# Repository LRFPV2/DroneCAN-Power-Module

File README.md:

# XRC Technologies DroneCAN Power Module

INSTRUCTIONS FOR USE: 
Checkout code and submodules. If sub-modules are not checked out, code will not compile properly due to broken dependencies.
```
git clone --recurse-submodules https://github.com/LRFPV2/DroneCAN-Power-Module.git
```
To flash to device, open project in PlatformIO and build "Micro-Node-No-Bootloader"

Go into STM32CubeIDE and open the file "firmware.bin" from folder .pio

Select "Download" to program to STM32 after connecting.

Version 2.0 to be released soon at https://xrctechnologies.com/

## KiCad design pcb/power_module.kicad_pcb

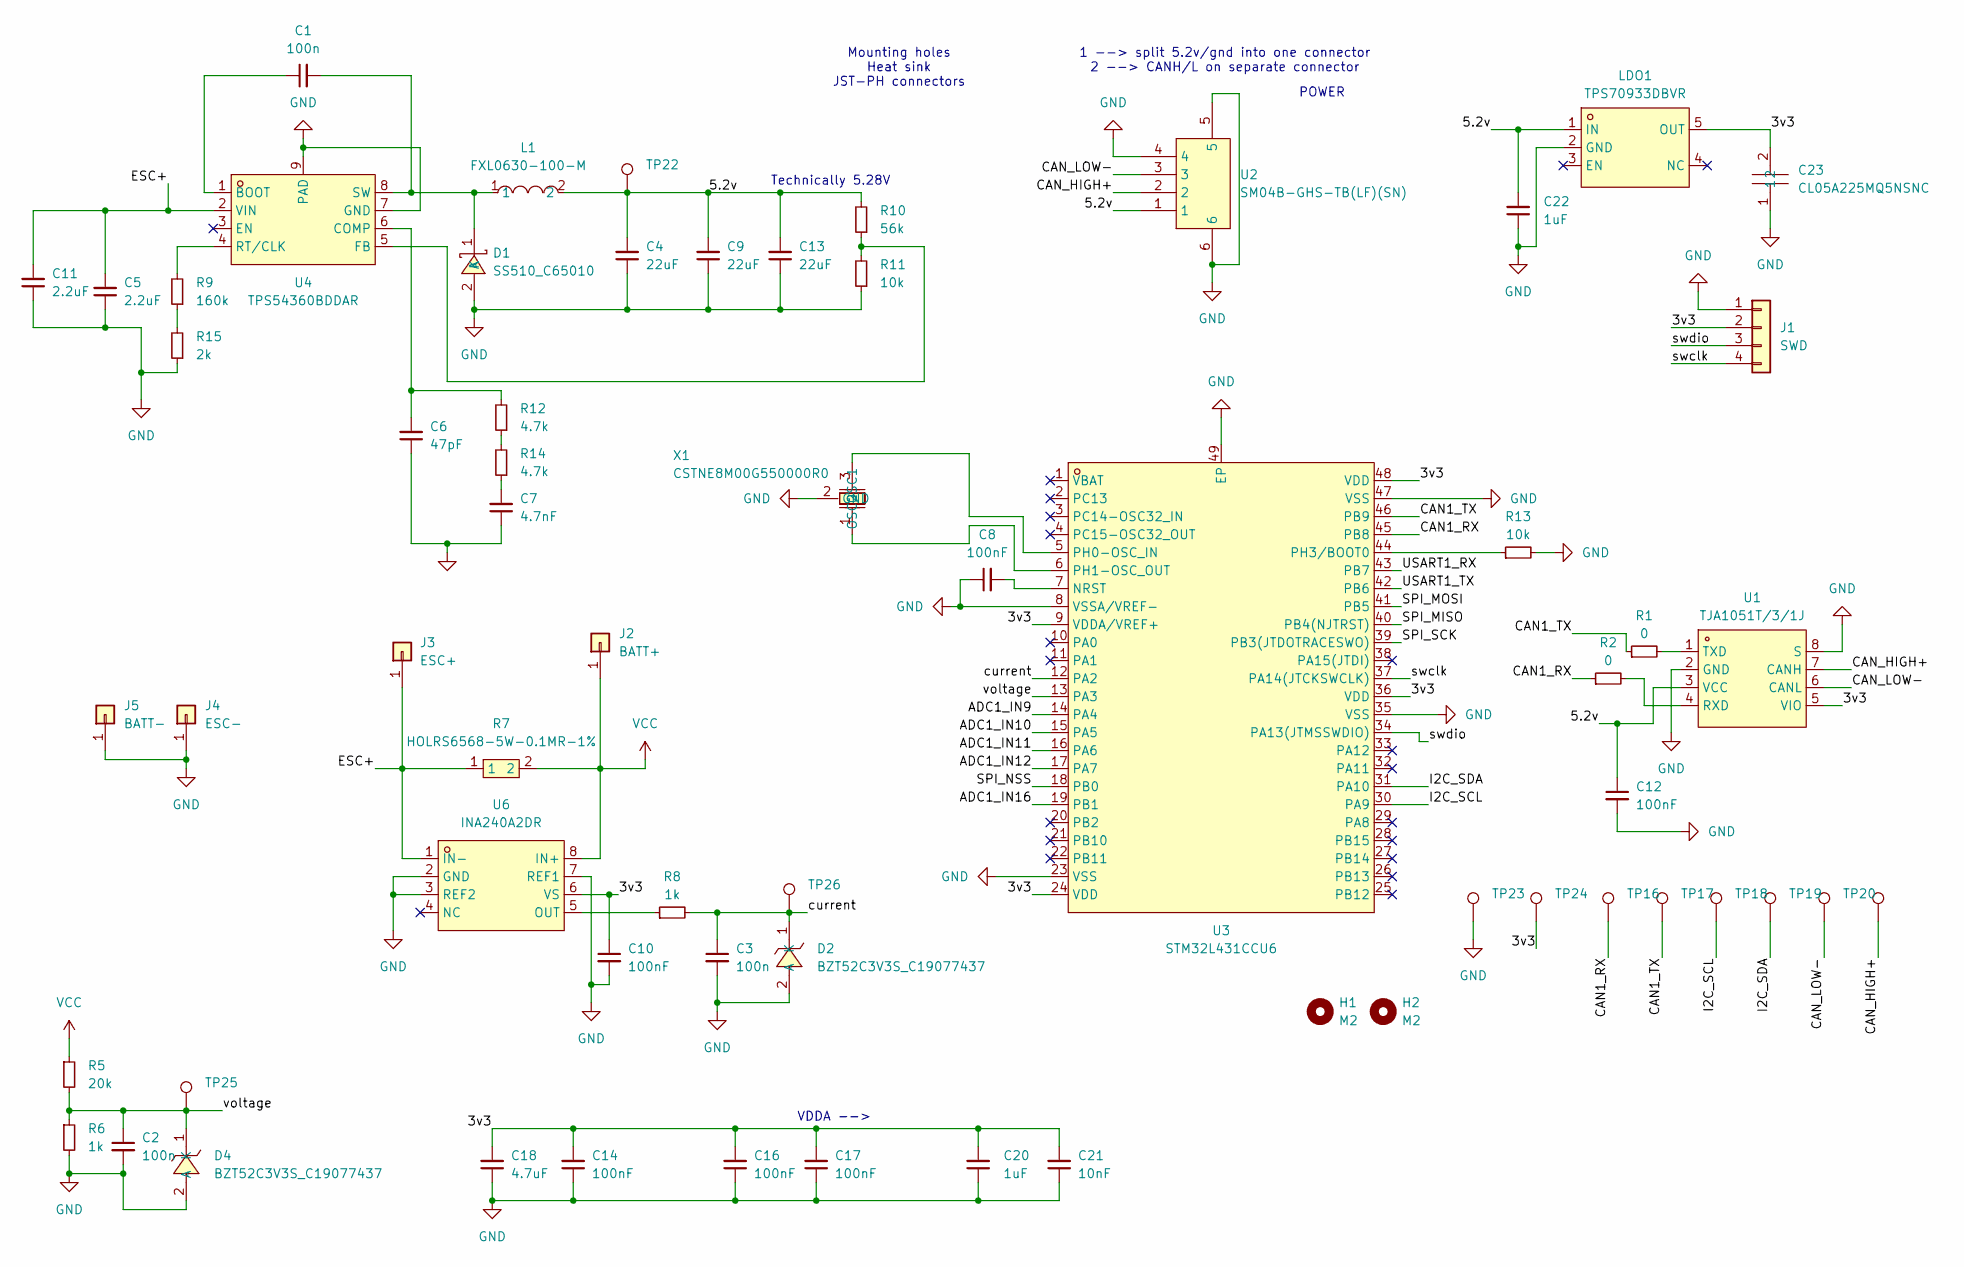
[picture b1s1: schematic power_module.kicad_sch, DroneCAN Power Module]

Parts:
C1, C2, C3: 100n; C_0402_1005Metric
C4, C9, C13: 22uF; C_0805_2012Metric
C5, C11: 2.2uF; C_1210_3225Metric
C6: 47pF; C_0402_1005Metric
C7: 4.7nF; C_0402_1005Metric
C8, C10, C12, C14, C16, C17: 100nF; C_0402_1005Metric
C18: 4.7uF; C_0402_1005Metric
C20, C22: 1uF; C_0402_1005Metric
C21: 10nF; C_0402_1005Metric
C23: CL05A225MQ5NSNC; C0402; LCSC Part C12530
D1: SS510_C65010; SMA_L4.3-W2.6-LS5.2-RD; LCSC Part C65010
D2, D4: BZT52C3V3S_C19077437; SOD-323_L1.7-W1.3-LS2.6-RD; LCSC Part C19077437
H1, H2: M2; MountingHole_2.2mm_M2
J1: SWD; PinHeader_1x04_P1.00mm_Vertical
J2: BATT+; Big-pad-0
J3: ESC+; Big-pad-0
J4: ESC-; Big-pad-0
J5: BATT-; Big-pad-0
L1: FXL0630-100-M; IND-SMD_L7.3-W6.8; LCSC Part C167223
LDO1: TPS70933DBVR; SOT-23-5_L3.0-W1.7-P0.95-LS2.8-BR; LCSC Part C89347
R1, R2: 0; R_0402_1005Metric
R5: 20k; R_0603_1608Metric
R6, R8: 1k; R_0402_1005Metric
R7: HOLRS6568-5W-0.1MR-1%; RES-SMD_L6.9-W6.6-A; LCSC Part C2927618
R9: 160k; R_0603_1608Metric
R10: 56k; R_0805_2012Metric
R11, R13: 10k; R_0402_1005Metric
R12, R14: 4.7k; R_0603_1608Metric
R15: 2k; R_0603_1608Metric
TP16, TP17, TP18, TP19, TP20, TP21, TP22, TP23, TP24, TP25, TP26: TestPoint_Pad_D1.0mm
U1: TJA1051T/3/1J; SOIC-8_L4.9-W3.9-P1.27-LS6.0-BL; LCSC Part C38695
U2: SM04B-GHS-TB(LF)(SN); CONN-SMD_4P-P1.25_SM04B-GHS-TB-LF-SN; LCSC Part C189895
U3: STM32L431CCU6; VQFN-48_L7.0-W7.0-P0.50-BL-EP5.5; LCSC Part C1337258
U4: TPS54360BDDAR; SOIC-8_L5.0-W4.0-P1.27-LS6.0-BL-EP2.0; LCSC Part C524806
U6: INA240A2DR; SOIC-8_L4.9-W3.9-P1.27-LS6.0-BL; LCSC Part C2060768
X1: CSTNE8M00G550000R0; OSC-SMD_3P-L3.2-W1.3-P1.20-L; LCSC Part C341522

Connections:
/3v3: C10.1, C14.2, C16.2, C17.2, C18.2, C20.2, C21.2, C23.2, J1.2, LDO1.5 (OUT), TP24.1, U1.5 (VIO), U3.9 (VDDA/VREF+), U3.24 (VDD), U3.36 (VDD), U3.48 (VDD), U6.6 (VS)
/5.2v: C4.2, C9.2, C12.1, C13.2, C22.2, L1.2, LDO1.1 (IN), R10.2, TP22.1, U1.3 (VCC), U2.1
/ADC1_IN9: U3.14 (PA4)
/ADC1_IN10: U3.15 (PA5)
/ADC1_IN11: U3.16 (PA6)
/ADC1_IN12: U3.17 (PA7)
/ADC1_IN16: U3.19 (PB1)
/CAN1_RX: R2.1, TP16.1, U3.45 (PB8)
/CAN1_TX: R1.1, TP17.1, U3.46 (PB9)
/CAN_HIGH+: TP21.1, U1.7 (CANH), U2.2
/CAN_LOW-: TP20.1, U1.6 (CANL), U2.3
/ESC+: C5.2, C11.2, J3.1, R7.1, U4.2 (VIN), U6.1 (IN-)
/I2C_SCL: TP18.1, U3.30 (PA9)
/I2C_SDA: TP19.1, U3.31 (PA10)
/SPI_MISO: U3.40 (PB4(NJTRST))
/SPI_MOSI: U3.41 (PB5)
/SPI_NSS: U3.18 (PB0)
/SPI_SCK: U3.39 (PB3(JTDOTRACESWO))
/USART1_RX: U3.43 (PB7)
/USART1_TX: U3.42 (PB6)
/current: C3.1, D2.1 (K), R8.2, TP26.1, U3.12 (PA2)
/swclk: J1.4, U3.37 (PA14(JTCKSWCLK))
/swdio: J1.3, U3.34 (PA13(JTMSSWDIO))
/voltage: C2.1, D4.1 (K), R5.2, R6.1, TP25.1, U3.13 (PA3)
GND: C2.2, C3.2, C4.1, C5.1, C6.1, C7.1, C8.1, C9.1, C10.2, C11.1, C12.2, C13.1, C14.1, C16.1, C17.1, C18.1, C20.1, C21.1, C22.1, C23.1, D1.2 (A), D2.2 (A), D4.2 (A), J1.1, J4.1, J5.1, LDO1.2 (GND), R6.2, R11.1, R13.2, R15.1, TP23.1, U1.2 (GND), U1.8 (S), U2.4, U2.5, U2.6, U3.8 (VSSA/VREF-), U3.23 (VSS), U3.35 (VSS), U3.47 (VSS), U3.49 (EP), U4.7 (GND), U4.9 (PAD), U6.2 (GND), U6.3 (REF2), U6.7 (REF1), X1.2 (GND)
unnamed: C7.2, R14.1
unnamed: C1.2, D1.1 (K), L1.1, U4.8 (SW)
unnamed: R12.1, R14.2
unnamed: R9.1, R15.2
unnamed: R2.2, U1.4 (RXD)
unnamed: R1.2, U1.1 (TXD)
unnamed: C8.2, U3.7 (NRST)
unnamed: U3.5 (PH0-OSC_IN), X1.3 (OSC2)
unnamed: U3.6 (PH1-OSC_OUT), X1.1 (OSC1)
unnamed: R13.1, U3.44 (PH3/BOOT0)
unnamed: C1.1, U4.1 (BOOT)
unnamed: C6.2, R12.2, U4.6 (COMP)
unnamed: R10.1, R11.2, U4.5 (FB)
unnamed: R9.2, U4.4 (RT/CLK)
unnamed: R8.1, U6.5 (OUT)
VCC: J2.1, R5.1, R7.2, U6.8 (IN+)

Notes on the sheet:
Mounting holes Heat sink JST-PH connectors
Technically 5.28V
POWER
VDDA -->
1 --> split 5.2v/gnd into one connector 2 --> CANH/L on separate connector

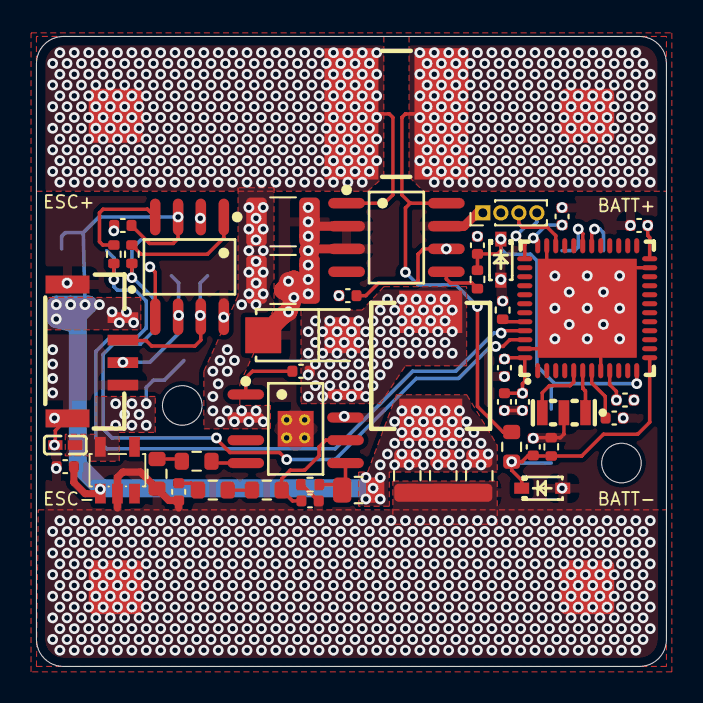
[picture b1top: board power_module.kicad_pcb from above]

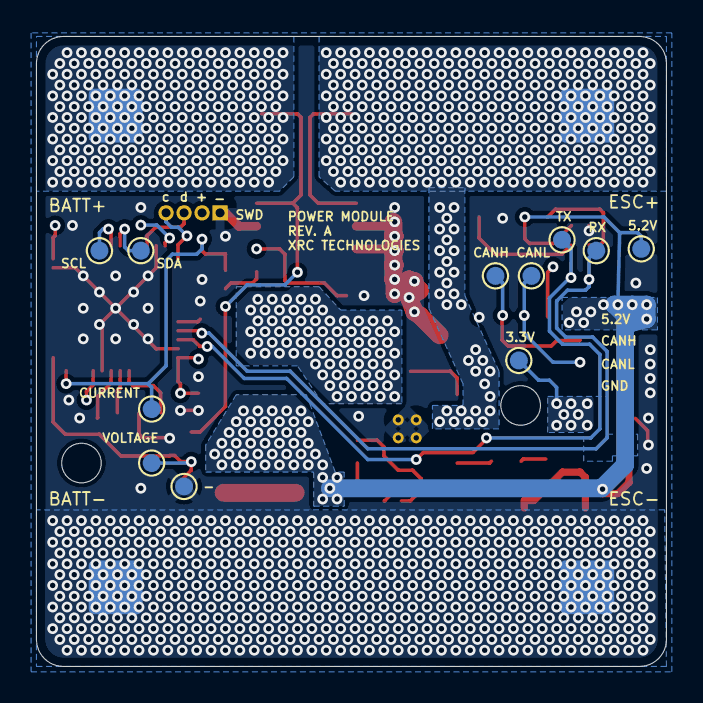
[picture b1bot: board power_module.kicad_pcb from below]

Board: 6 copper layers, 35.0 x 35.0 mm, 63 parts (11 on the bottom side), 30 nets.

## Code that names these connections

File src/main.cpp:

// XRC Technologies DroneCAN Power Module

#include <Arduino.h>
#include <dronecan.h>
#include <IWatchdog.h>
#include <app.h>
#include <vector>
#include <simple_dronecanmessages.h>

// Calculations:
// 0.1mOhm resistor
// 20k-1k voltage divider
// Vout = Vbatt / 21
// 12-bit ADC (4096 bit resolution)
// INA240A2 --> 50V/V Gain
// Voltage (ADC)= I * 0.0001 * 50 = 3.3/4096
// Voltage (ADC) = 3.3/4096 = V_batt / 21
// Target current: 200A
// These are good starting numbers but actual numbers may vary
// I_batt = 0.0064453125 * V_adc
// V_batt = 0.0169189453125 * V_adc
// 1 / I_batt constant = 155.151515
// 1 / V_batt constant = 59.1053391

#define SHUNT_RESISTANCE 0.0025
#define CURRENT_SCALE_FACTOR 1.623
#define VOLTAGE_SCALE_FACTOR 14.705
#define CURRENT_PIN PA2
#define VOLTAGE_PIN PA3

float current;
float voltage;

std::vector<DroneCAN::parameter> custom_parameters = {
    {"NODEID", UAVCAN_PROTOCOL_PARAM_VALUE_INTEGER_VALUE, 127, 0, 127}};

DroneCAN dronecan;

uint32_t looptime = 0;

static void onTransferReceived(CanardInstance *ins, CanardRxTransfer *transfer)
{
    DroneCANonTransferReceived(dronecan, ins, transfer);
}

static bool shouldAcceptTransfer(const CanardInstance *ins,
                                 uint64_t *out_data_type_signature,
                                 uint16_t data_type_id,
                                 CanardTransferType transfer_type,
                                 uint8_t source_node_id)

{
    return false || DroneCANshoudlAcceptTransfer(ins, out_data_type_signature, data_type_id, transfer_type, source_node_id);
}

void setup()
{
    app_setup();
    IWatchdog.begin(2000000); 
    Serial.begin(115200);
    dronecan.version_major = 1;
    dronecan.version_minor = 0;
    dronecan.init(
        onTransferReceived, 
        shouldAcceptTransfer, 
        custom_parameters,
        "XRC Technologies Power Module"
    );
    pinMode(CURRENT_PIN, INPUT);
    pinMode(VOLTAGE_PIN, INPUT);

    while (true)
    {
        const uint32_t now = millis();

        // send our battery message at 10Hz
        if (now - looptime > 100)
        {
            looptime = millis();

            // construct dronecan packet
            current = analogRead(CURRENT_PIN) / CURRENT_SCALE_FACTOR;
            voltage = analogRead(VOLTAGE_PIN) / VOLTAGE_SCALE_FACTOR;
            uavcan_equipment_power_BatteryInfo pkt{};
            pkt.voltage = voltage;
            pkt.current = current;
            //pkt.temperature = INA.getTemperature();

            sendUavcanMsg(dronecan.canard, pkt);
        }

        dronecan.cycle();
        IWatchdog.reload();
    }
}

void loop()
{
    // Doesn't work coming from bootloader ? use while loop in setup
}

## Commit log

2025-04-02 link fix
2025-04-02 fix logo
2025-04-23 trying
2025-05-02 change readme image
2025-05-06 working bootloader
2025-05-06 tidy + params working
2025-05-07 tidy up custom params setting
2025-05-07 debugging notes
2025-05-07 spelling
2025-05-07 Fix submodules to tags
2025-05-07 update examples
2025-05-07 update example readme
2025-05-07 1.2 (#7)
    * bring in 1.2 library changes
    * Update ArduinoDroneCANlib reference to 1.2
2025-05-07 New example
2025-06-15 1.3 library changes (#12)
    - Allow bootloaderless switching
    - force node allocation in library initialisation to make sure we get CAN connection before user code has opportunity to crash
    - Fix node id bug on a new node
    - Format, restructure and add comments
    - Add simple messages support
    * 1.2.1 library changes
2025-06-22 Allow flashing bootloader and app at the same time (#14)
2025-06-22 V1.3 examples api update (#17)
    * trial .ini
    * working!
    * example update
2025-06-24 ID Updates
2025-06-24 de69
2025-06-26 allow .bin to be generatured during upload & move watchdog (#19)
    * allow .bin to be generatured during upload & move watchdog
    * update examples to match 1.3.1 style
2025-07-21 Integrate DNA bug fix (#20)
2025-07-22 Add default platformio build option (#21)
    * Add default platformio config option
2025-07-28 written and tested MCP9600 example (#22)
2025-08-06 Update README.md (#23)
2025-08-17 Update V1.1 image (#24)
2025-10-18 initial code commit
2025-10-18 Added schematic
2025-10-18 Added hardware design files
2025-10-20 Calibrated scaling facotrs
2025-10-20 Added compiled binary
